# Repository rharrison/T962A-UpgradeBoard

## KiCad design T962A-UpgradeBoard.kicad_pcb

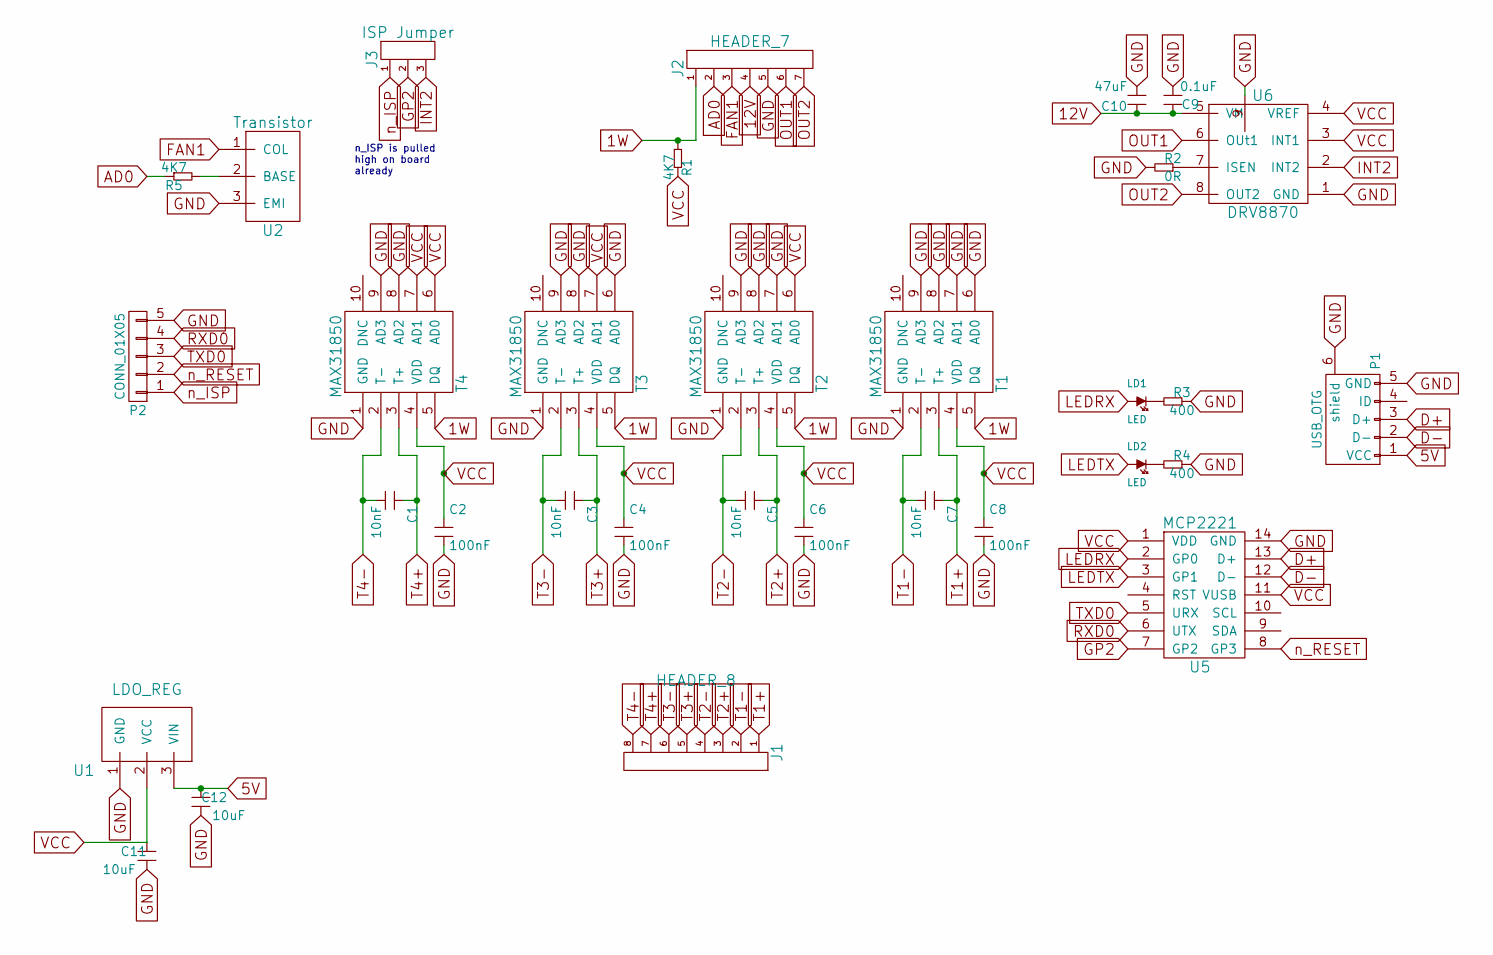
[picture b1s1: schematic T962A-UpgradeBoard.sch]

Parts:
C1, C3, C5, C7: 10nF; c_0603
C2, C4, C6, C8: 100nF; c_0603
C9: 0.1uF; C_0603
C10: 47uF; CP_5x11mm
C11, C12: 10uF; C_0603
J1: HEADER_8; mpt_0,5%2f8-2,54
J2: HEADER_7; mpt_0,5%2f7-2,54
J3: ISP Jumper; Pin_Header_Straight_1x03
LD1, LD2: LED; Led_0603
P1: USB_OTG; USB_Micro-B
P2: CONN_01X05; Pin_Header_Straight_1x05
R1, R5: 4K7; r_0603
R2: 0R; r_1206
R3, R4: 400; r_0603
T1, T2, T3, T4: MAX31850; MAX31850_MAX31851_TDFN_EP
U1: LDO_REG; sot223
U2: Transistor; TO-92_Inline_Narrow_Oval
U5: MCP2221; tssop-14
U6: DRV8870; HSOP-8

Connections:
1W: J2.1, R1.2, T1.5 (DQ), T2.5 (DQ), T3.5 (DQ), T4.5 (DQ)
5V: C12.1, P1.1 (VCC), U1.3 (VIN)
12V: C9.1, C10.1, J2.4, U6.5 (VM)
AD0: J2.2, R5.1
D+: P1.3 (D+), U5.13 (D+)
D-: P1.2 (D-), U5.12 (D-)
FAN1: J2.3, U2.1 (COL)
GND: C2.2, C4.2, C6.2, C8.2, C9.2, C10.2, C11.2, C12.2, J2.5, P1.5 (GND), P1.6 (shield), P2.5, R2.2, R3.1, R4.1, T1.1 (GND), T1.6 (AD0), T1.7 (AD1), T1.8 (AD2), T1.9 (AD3), T2.1 (GND), T2.7 (AD1), T2.8 (AD2), T2.9 (AD3), T3.1 (GND), T3.6 (AD0), T3.8 (AD2), T3.9 (AD3), T4.1 (GND), T4.8 (AD2), T4.9 (AD3), U1.1 (GND), U2.3 (EMI), U5.14 (GND), U6.1 (GND), U6.9
GP2: J3.2, U5.7 (GP2)
INT2: J3.3, U6.2 (INT2)
LEDRX: LD1.1 (A), U5.2 (GP0)
LEDTX: LD2.1 (A), U5.3 (GP1)
unnamed: LD1.2 (K), R3.2
unnamed: LD2.2 (K), R4.2
unnamed: R2.1, U6.7 (ISEN)
unnamed: R5.2, U2.2 (BASE)
OUT1: J2.6, U6.6 (OUt1)
OUT2: J2.7, U6.8 (OUT2)
RXD0: P2.4, U5.6 (UTX)
T1+: C7.1, J1.1, T1.3 (T+)
T1-: C7.2, J1.2, T1.2 (T-)
T2+: C5.1, J1.3, T2.3 (T+)
T2-: C5.2, J1.4, T2.2 (T-)
T3+: C3.1, J1.5, T3.3 (T+)
T3-: C3.2, J1.6, T3.2 (T-)
T4+: C1.1, J1.7, T4.3 (T+)
T4-: C1.2, J1.8, T4.2 (T-)
TXD0: P2.3, U5.5 (URX)
VCC: C2.1, C4.1, C6.1, C8.1, C11.1, R1.1, T1.4 (VDD), T2.4 (VDD), T2.6 (AD0), T3.4 (VDD), T3.7 (AD1), T4.4 (VDD), T4.6 (AD0), T4.7 (AD1), U1.2 (VCC), U5.1 (VDD), U5.11 (VUSB), U6.3 (INT1), U6.4 (VREF)
n_ISP: J3.1, P2.1
n_RESET: P2.2, U5.8 (GP3)

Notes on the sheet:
n_ISP is pulled high on board already

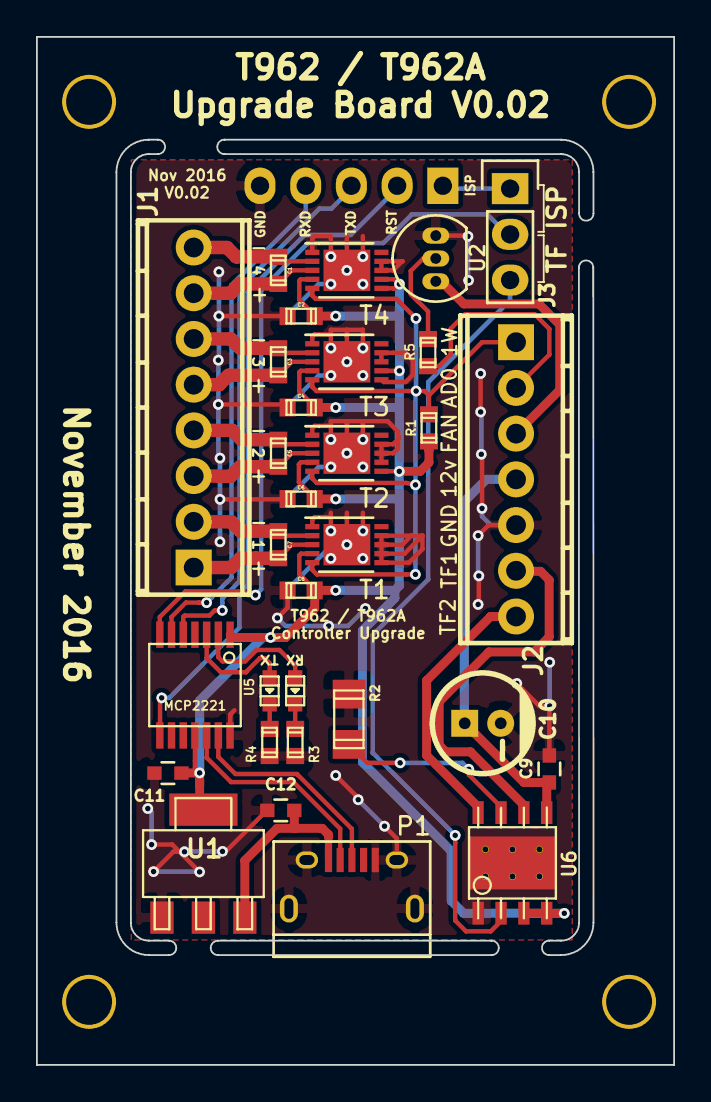
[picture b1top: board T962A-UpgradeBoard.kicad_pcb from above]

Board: 2 copper layers, 35.4 x 57.1 mm, 32 parts (1 on the bottom side), 31 nets.

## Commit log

2016-11-10 Version 0.02 Signed-off-by: Robert Harrison <rharrison@hgf.com>
2016-11-17 T962 Images Updated
2016-11-17 Image Update
